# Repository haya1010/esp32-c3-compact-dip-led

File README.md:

# ESP32-C3 Compact DIP + LED PWM

ESP32-C3-WROOM-02を2.54 mmピッチで引き出し、5/12/24 VのDC入力またはUSB-C 5 Vで動かせる、1チャンネルLED PWM基板です。基板寸法は **50 × 78 mm**。USB-Cは電源専用で、書き込みはM5Stack A105ヘッダから行います。

## 主な仕様

- DCジャック: 5.5/2.1 mm、センタープラス、5～24 V
- USB-C: 5 V電源専用。D+/D-は未接続、CC1/CC2に各5.1 kΩ
- 3.3 V電源: LMR36510（最大入力65 V）による直接降圧
- 降圧インダクタ: 22µH、定格2A、飽和電流3.1Aの低価格モールド品
- JP1: USB 5 VかDC入力を手動選択
- JP2: 基板内3.3 VかA105の3.3 Vを手動選択
- 書き込み: M5Stack A105用6ピン（GND、BOOT、EN、TXD、RXD、3V3）
- LED出力: J3-1がLED+、J3-2がMOSFETでPWMされるLED-
- PWM: GPIO4、N-MOSFET 1チャンネル
- JLCPCBでSMD実装、DCジャック・端子台・ピンヘッダは手はんだ

## 最重要ルール

1. JP1は1-2（USB）または2-3（DC）の片側だけをはんだで接続します。
2. JP2は1-2（内蔵3.3 V）または2-3（A105給電）の片側だけを接続します。
3. DCジャックとUSB-Cを同時に給電しません。
4. A105から給電する時はJP2をA105側にし、DC/USB電源を外します。
5. DCジャックはセンタープラス限定です。本基板に逆接保護・ヒューズ・自動ORingはありません。

詳しい説明は [電源・ジャンパガイド](docs/POWER_AND_JUMPER_GUIDE_JA.md) と [注文前レビュー](ORDER_REVIEW.md) を参照してください。

## 製造ファイル

- `manufacturing/JLCPCB-upload.zip`: PCB製造用Gerber/ドリル一式
- `BOM-JLCPCB.csv`: PCBA用BOM
- `CPL-JLCPCB.csv`: PCBA用部品座標
- `BOM-full.csv`: 手はんだ部品を含む全部品表
- `verification/erc.rpt`: ERC 0件
- `verification/drc.rpt`: DRC 0件、未配線0件

JLCPCBへの注文はまだ行っていません。注文画面で部品在庫、向き、価格を確認してから発注してください。

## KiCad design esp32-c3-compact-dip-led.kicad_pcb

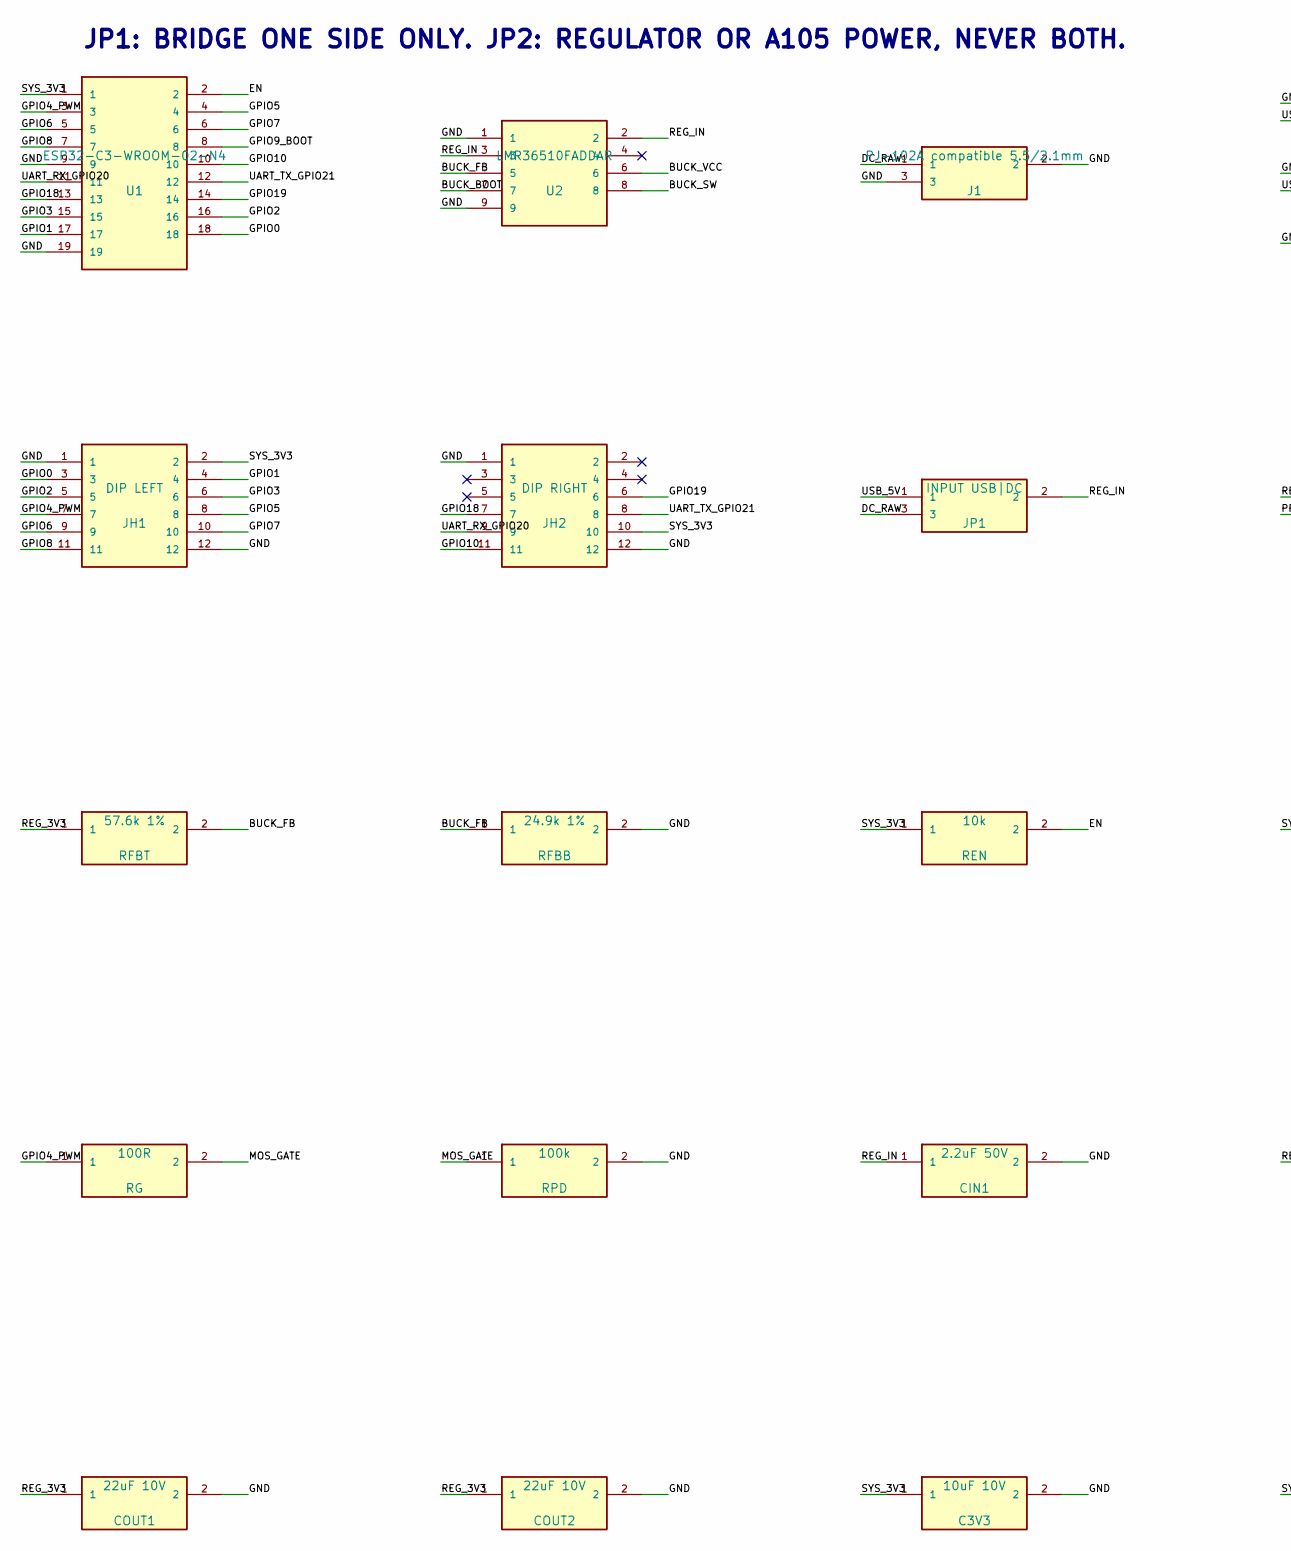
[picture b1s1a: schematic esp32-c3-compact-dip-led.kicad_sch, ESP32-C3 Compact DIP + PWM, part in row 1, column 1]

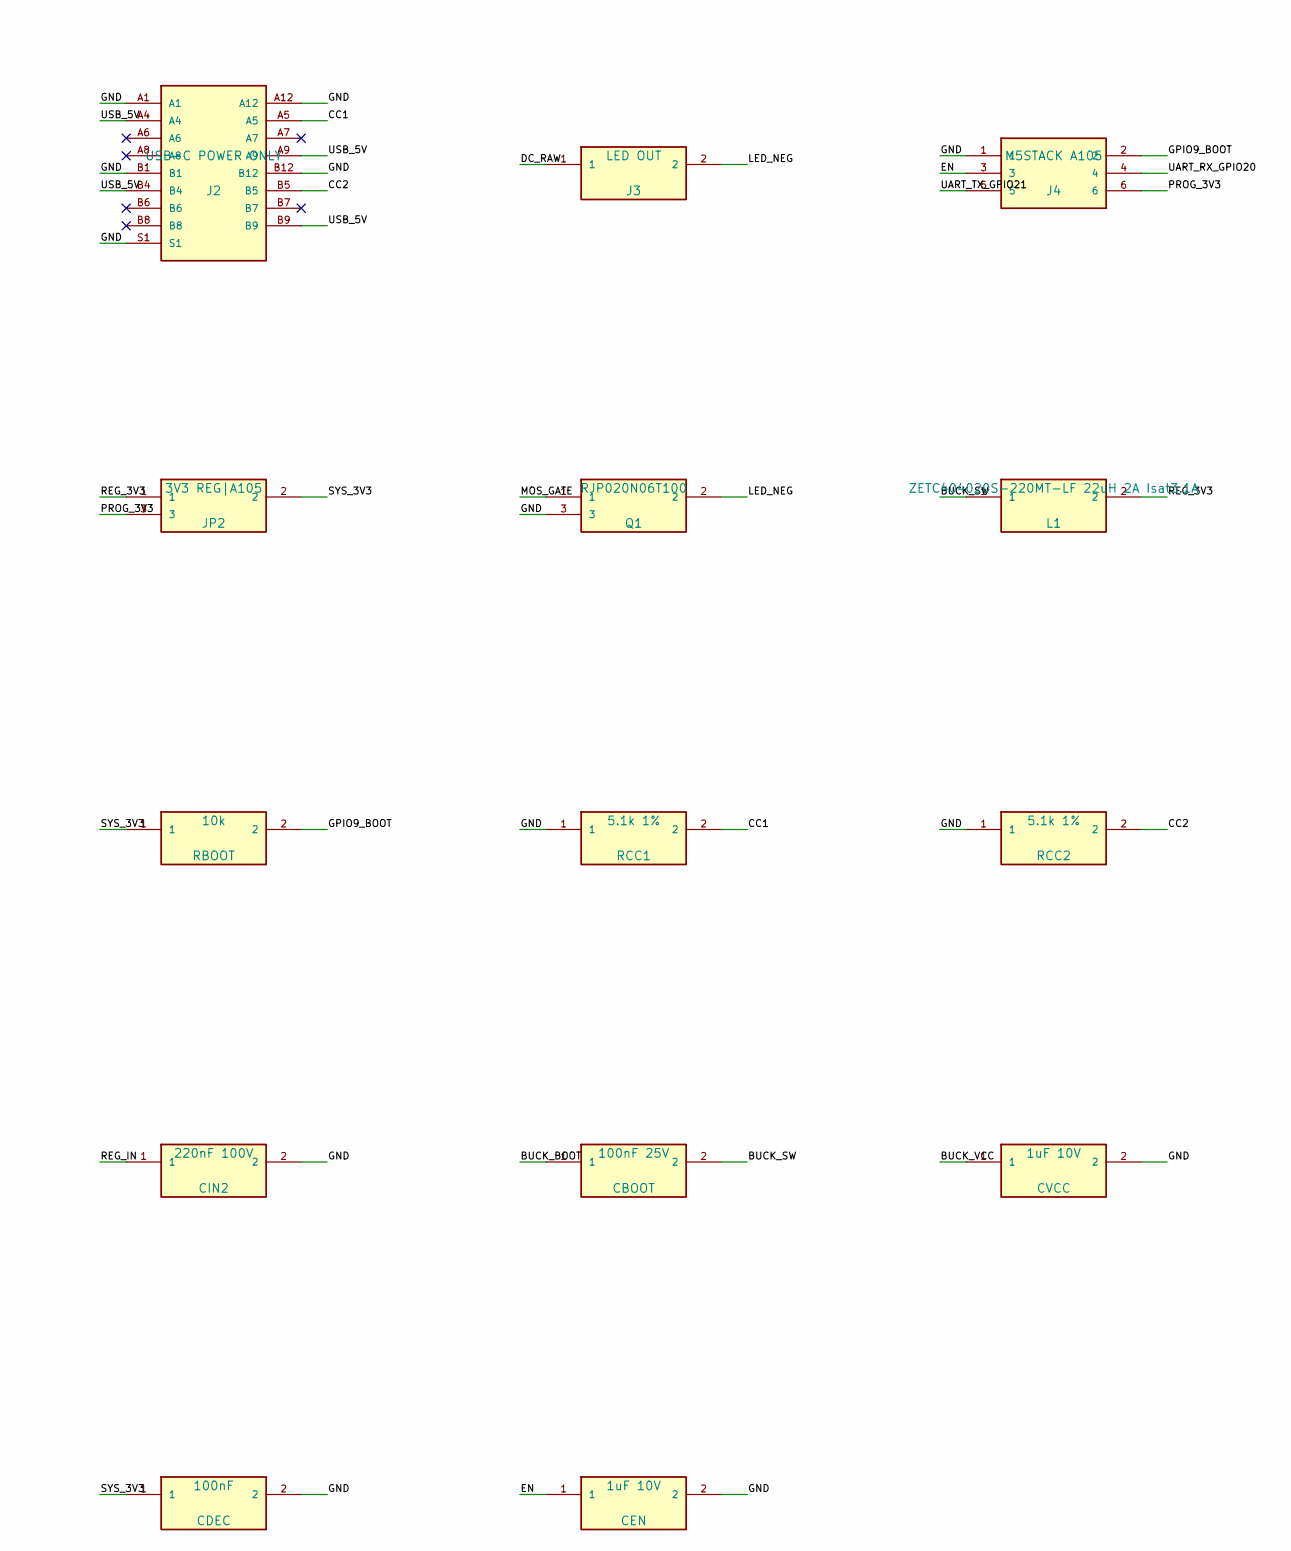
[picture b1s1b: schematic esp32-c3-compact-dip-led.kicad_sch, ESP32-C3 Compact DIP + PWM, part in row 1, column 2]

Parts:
C3V3: 10uF 10V
CBOOT: 100nF 25V
CDEC: 100nF
CEN: 1uF 10V
CIN1: 2.2uF 50V
CIN2: 220nF 100V
COUT1, COUT2: 22uF 10V
CVCC: 1uF 10V
J1: PJ-102A compatible 5.5/2.1mm
J2: USB-C POWER ONLY
J3: LED OUT
J4: M5STACK A105
JH1: DIP LEFT
JH2: DIP RIGHT
JP1: INPUT USB|DC
JP2: 3V3 REG|A105
L1: ZETC404020S-220MT-LF 22uH 2A Isat3.1A
Q1: RJP020N06T100
RBOOT: 10k
RCC1, RCC2: 5.1k 1%
REN: 10k
RFBB: 24.9k 1%
RFBT: 57.6k 1%
RG: 100R
RPD: 100k
U1: ESP32-C3-WROOM-02-N4
U2: LMR36510FADDAR

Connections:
BUCK_BOOT: CBOOT.1, U2.7
BUCK_FB: RFBB.1, RFBT.2, U2.5
BUCK_SW: CBOOT.2, L1.1, U2.8
BUCK_VCC: CVCC.1, U2.6
CC1: J2.A5, RCC1.2
CC2: J2.B5, RCC2.2
DC_RAW: J1.1, J3.1, JP1.3
EN: CEN.1, J4.3, REN.2, U1.2
GND: C3V3.2, CDEC.2, CEN.2, CIN1.2, CIN2.2, COUT1.2, COUT2.2, CVCC.2, J1.2, J1.3, J2.A1, J2.A12, J2.B1, J2.B12, J2.S1, J4.1, JH1.1, JH1.12, JH2.1, JH2.12, Q1.3, RCC1.1, RCC2.1, RFBB.2, RPD.2, U1.9, U1.19, U2.1, U2.9
GPIO0: JH1.3, U1.18
GPIO1: JH1.4, U1.17
GPIO2: JH1.5, U1.16
GPIO3: JH1.6, U1.15
GPIO4_PWM: JH1.7, RG.1, U1.3
GPIO5: JH1.8, U1.4
GPIO6: JH1.9, U1.5
GPIO7: JH1.10, U1.6
GPIO8: JH1.11, U1.7
GPIO9_BOOT: J4.2, RBOOT.2, U1.8
GPIO10: JH2.11, U1.10
GPIO18: JH2.7, U1.13
GPIO19: JH2.6, U1.14
LED_NEG: J3.2, Q1.2
MOS_GATE: Q1.1, RG.2, RPD.1
PROG_3V3: J4.6, JP2.3
REG_3V3: COUT1.1, COUT2.1, JP2.1, L1.2, RFBT.1
REG_IN: CIN1.1, CIN2.1, JP1.2, U2.2, U2.3
SYS_3V3: C3V3.1, CDEC.1, JH1.2, JH2.10, JP2.2, RBOOT.1, REN.1, U1.1
UART_RX_GPIO20: J4.4, JH2.9, U1.11
UART_TX_GPIO21: J4.5, JH2.8, U1.12
USB_5V: J2.A4, J2.A9, J2.B4, J2.B9, JP1.1

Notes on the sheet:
JP1: BRIDGE ONE SIDE ONLY. JP2: REGULATOR OR A105 POWER, NEVER BOTH.

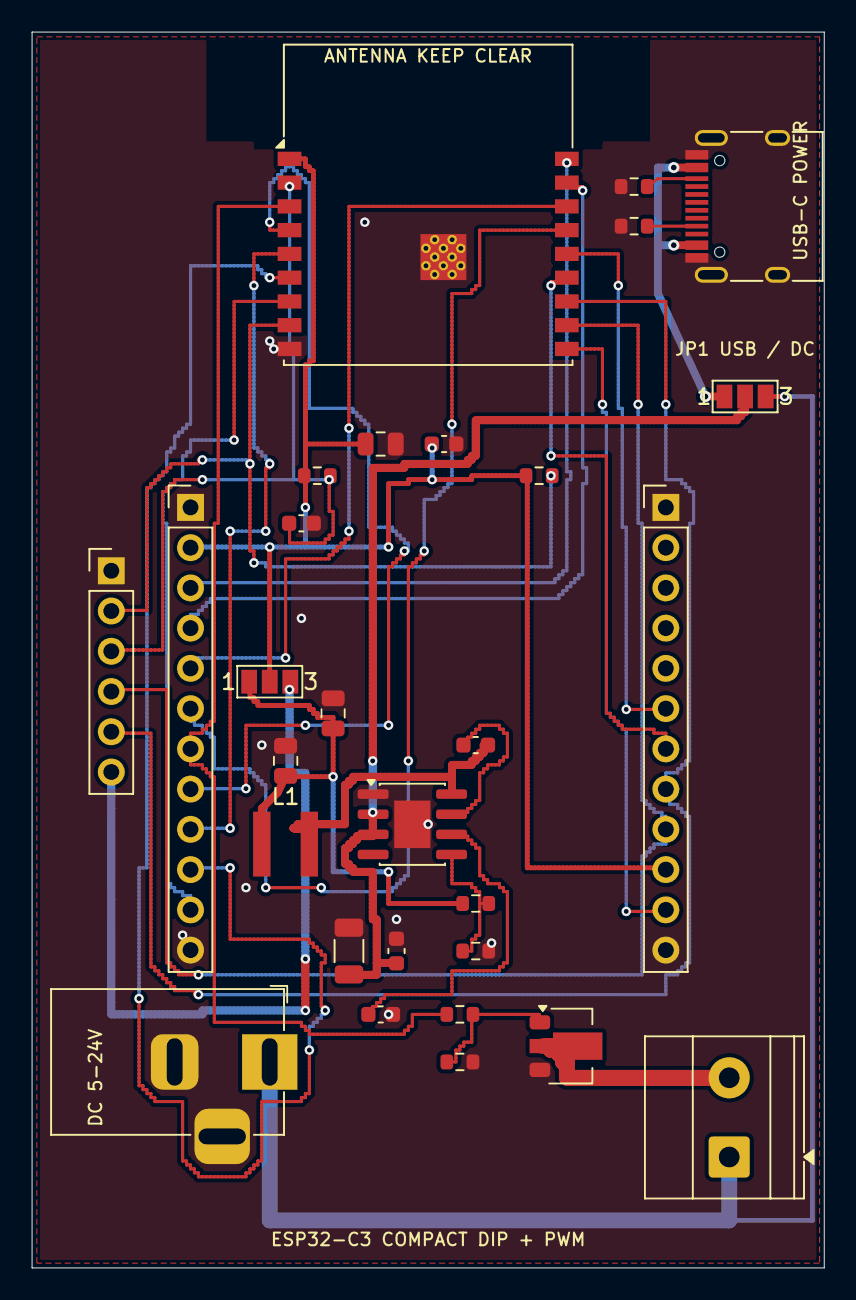
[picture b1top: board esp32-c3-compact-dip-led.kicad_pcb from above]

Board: 2 copper layers, 50.0 x 78.0 mm, 29 parts (0 on the bottom side), 31 nets.

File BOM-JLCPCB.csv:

Comment,Designator,Footprint,LCSC Part #
ESP32-C3-WROOM-02-N4,U1,ESP32-C3-WROOM-02,C2934560
LMR36510FADDAR,U2,SOIC-8-1EP_3.9x4.9mm_P1.27mm_EP2.29x3mm,C1858394
USB-C POWER ONLY,J2,USB_C_Receptacle_HRO_TYPE-C-31-M-12,C165948
RJP020N06T100,Q1,SOT-89-3,C703680
ZETC404020S-220MT-LF 22uH 2A Isat3.1A,L1,ZETC404020S-220MT-LF,C49009349
57.6k 1%,RFBT,R_0603_1608Metric,C23206
24.9k 1%,RFBB,R_0603_1608Metric,C25843
10k,REN,R_0603_1608Metric,C25804
10k,RBOOT,R_0603_1608Metric,C25804
5.1k 1%,RCC1,R_0603_1608Metric,C23186
5.1k 1%,RCC2,R_0603_1608Metric,C23186
100R,RG,R_0603_1608Metric,C22775
100k,RPD,R_0603_1608Metric,C25803
2.2uF 50V,CIN1,C_1206_3216Metric,C23630
220nF 100V,CIN2,C_0603_1608Metric,C282519
100nF 25V,CBOOT,C_0603_1608Metric,C14663
1uF 10V,CVCC,C_0603_1608Metric,C15849
22uF 10V,COUT1,C_0805_2012Metric,C45783
22uF 10V,COUT2,C_0805_2012Metric,C45783
10uF 10V,C3V3,C_0805_2012Metric,C15850
100nF,CDEC,C_0603_1608Metric,C14663
1uF 10V,CEN,C_0603_1608Metric,C15849
